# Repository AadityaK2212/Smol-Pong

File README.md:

# Smol-Pong
It is a mini console that can run a 2 player pong game using a coin cell battery and a 8X8 LED grid. ioriginally saw someoemake a smal buiness card that can play video games, so I elaborated off of that and made it to only play pong I also created one for flappy bird. It runs on an ATtiny 1616 Microcontroller.

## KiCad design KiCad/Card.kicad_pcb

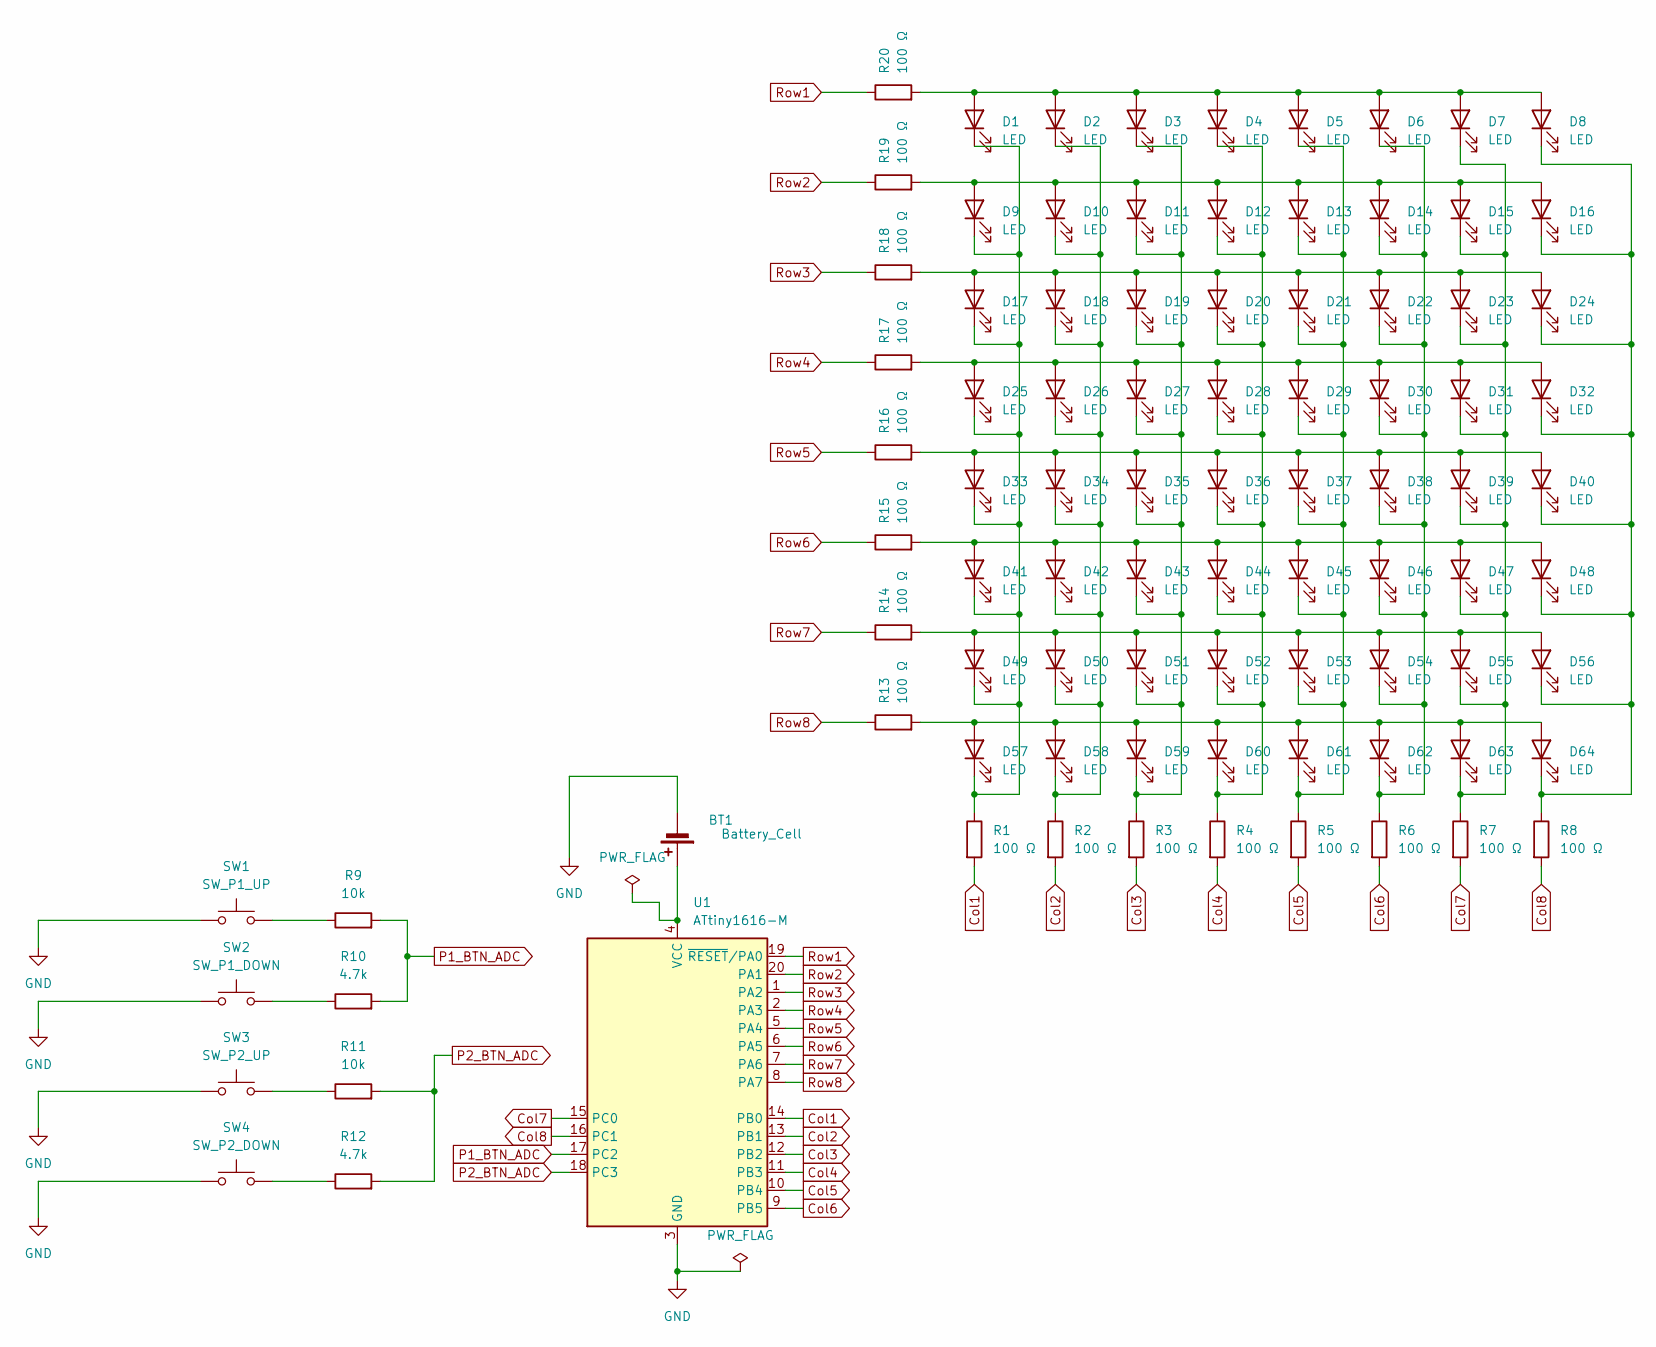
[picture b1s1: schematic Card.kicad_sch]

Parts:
BT1: Battery_Cell; BatteryHolder_Keystone_1057_1x2032
D1, D2, D3, D4, D5, D6, D7, D8, D9, D10, D11, D12, D13, D14, D15, D16, D17, D18, D19, D20, D21, D22, D23, D24, D25, D26, D27, D28, D29, D30, D31, D32, D33, D34, D35, D36, D37, D38, D39, D40, D41, D42, D43, D44, D45, D46, D47, D48, D49, D50, D51, D52, D53, D54, D55, D56, D57, D58, D59, D60, D61, D62, D63, D64: LED; LED_0603_1608Metric
R1, R2, R3, R4, R5, R6, R7, R8, R13, R14, R15, R16, R17, R18, R19, R20: 100 Ω; R_0603_1608Metric
R9, R11: 10k; R_0603_1608Metric
R10, R12: 4.7k; R_0603_1608Metric
SW1: SW_P1_UP; SW_SPST_TL3342
SW2: SW_P1_DOWN; SW_SPST_TL3342
SW3: SW_P2_UP; SW_SPST_TL3342
SW4: SW_P2_DOWN; SW_SPST_TL3342
U1: ATtiny1616-M; VQFN-20-1EP_3x3mm_P0.4mm_EP1.7x1.7mm

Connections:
Col1: R1.2, U1.14 (PB0)
Col2: R2.2, U1.13 (PB1)
Col3: R3.2, U1.12 (PB2)
Col4: R4.2, U1.11 (PB3)
Col5: R5.2, U1.10 (PB4)
Col6: R6.2, U1.9 (PB5)
Col7: R7.2, U1.15 (PC0)
Col8: R8.2, U1.16 (PC1)
GND: BT1.2 (-), SW1.1, SW2.1, SW3.1, SW4.1, U1.3 (GND), U1.21 (GND)
unnamed: BT1.1 (+), U1.4 (VCC)
unnamed: D1.2 (A), D2.2 (A), D3.2 (A), D4.2 (A), D5.2 (A), D6.2 (A), D7.2 (A), D8.2 (A), R20.2
unnamed: D1.1 (K), D9.1 (K), D17.1 (K), D25.1 (K), D33.1 (K), D41.1 (K), D49.1 (K), D57.1 (K), R1.1
unnamed: D9.2 (A), D10.2 (A), D11.2 (A), D12.2 (A), D13.2 (A), D14.2 (A), D15.2 (A), D16.2 (A), R19.2
unnamed: D2.1 (K), D10.1 (K), D18.1 (K), D26.1 (K), D34.1 (K), D42.1 (K), D50.1 (K), D58.1 (K), R2.1
unnamed: D3.1 (K), D11.1 (K), D19.1 (K), D27.1 (K), D35.1 (K), D43.1 (K), D51.1 (K), D59.1 (K), R3.1
unnamed: D4.1 (K), D12.1 (K), D20.1 (K), D28.1 (K), D36.1 (K), D44.1 (K), D52.1 (K), D60.1 (K), R4.1
unnamed: D5.1 (K), D13.1 (K), D21.1 (K), D29.1 (K), D37.1 (K), D45.1 (K), D53.1 (K), D61.1 (K), R5.1
unnamed: D6.1 (K), D14.1 (K), D22.1 (K), D30.1 (K), D38.1 (K), D46.1 (K), D54.1 (K), D62.1 (K), R6.1
unnamed: D7.1 (K), D15.1 (K), D23.1 (K), D31.1 (K), D39.1 (K), D47.1 (K), D55.1 (K), D63.1 (K), R7.1
unnamed: D8.1 (K), D16.1 (K), D24.1 (K), D32.1 (K), D40.1 (K), D48.1 (K), D56.1 (K), D64.1 (K), R8.1
unnamed: D17.2 (A), D18.2 (A), D19.2 (A), D20.2 (A), D21.2 (A), D22.2 (A), D23.2 (A), D24.2 (A), R18.2
unnamed: D25.2 (A), D26.2 (A), D27.2 (A), D28.2 (A), D29.2 (A), D30.2 (A), D31.2 (A), D32.2 (A), R17.2
unnamed: D33.2 (A), D34.2 (A), D35.2 (A), D36.2 (A), D37.2 (A), D38.2 (A), D39.2 (A), D40.2 (A), R16.2
unnamed: D41.2 (A), D42.2 (A), D43.2 (A), D44.2 (A), D45.2 (A), D46.2 (A), D47.2 (A), D48.2 (A), R15.2
unnamed: D49.2 (A), D50.2 (A), D51.2 (A), D52.2 (A), D53.2 (A), D54.2 (A), D55.2 (A), D56.2 (A), R14.2
unnamed: D57.2 (A), D58.2 (A), D59.2 (A), D60.2 (A), D61.2 (A), D62.2 (A), D63.2 (A), D64.2 (A), R13.2
unnamed: R9.1, SW1.2
unnamed: R10.1, SW2.2
unnamed: R11.1, SW3.2
unnamed: R12.1, SW4.2
P1_BTN_ADC: R9.2, R10.2, U1.17 (PC2)
P2_BTN_ADC: R11.2, R12.2, U1.18 (PC3)
Row1: R20.1, U1.19 (~RESET/PA0)
Row2: R19.1, U1.20 (PA1)
Row3: R18.1, U1.1 (PA2)
Row4: R17.1, U1.2 (PA3)
Row5: R16.1, U1.5 (PA4)
Row6: R15.1, U1.6 (PA5)
Row7: R14.1, U1.7 (PA6)
Row8: R13.1, U1.8 (PA7)

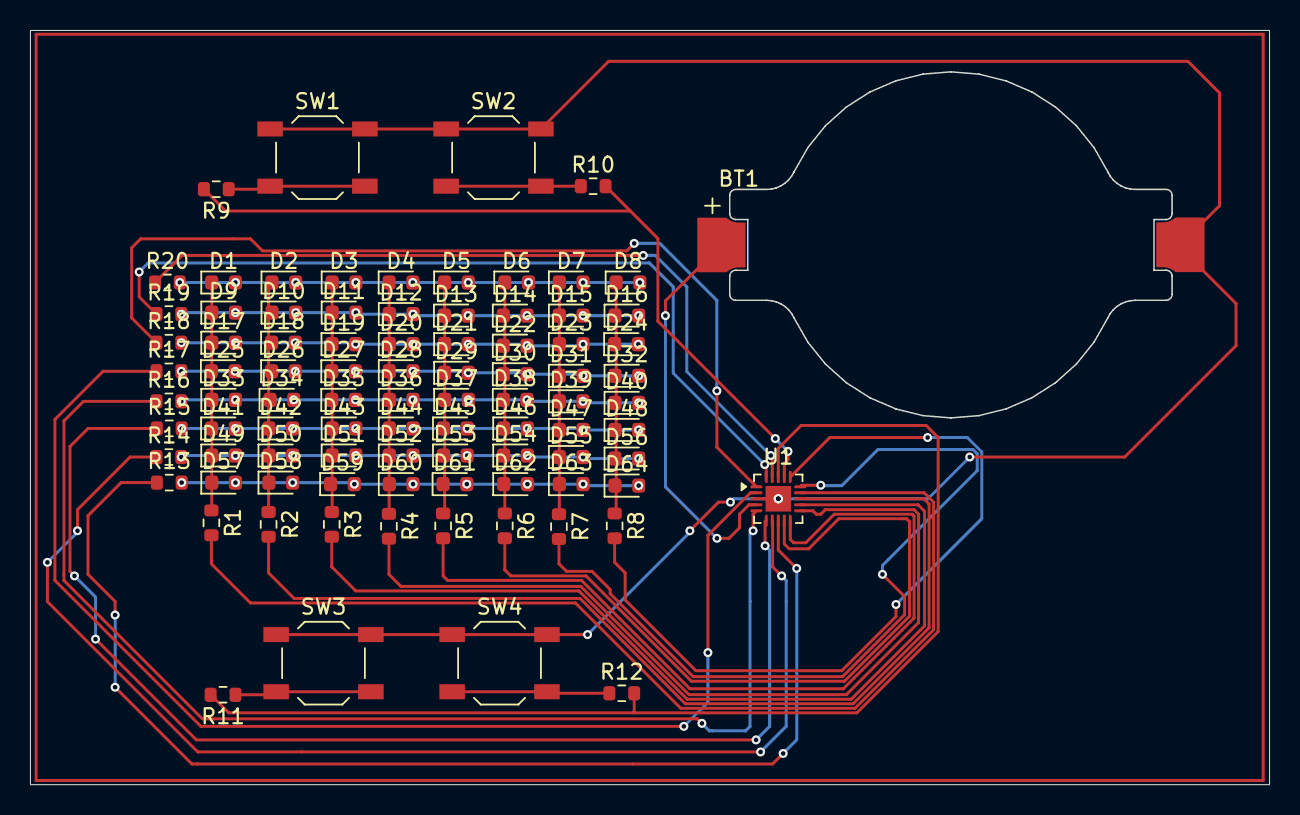
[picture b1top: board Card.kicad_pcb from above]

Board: 2 copper layers, 82.3 x 50.1 mm, 90 parts (0 on the bottom side), 40 nets.

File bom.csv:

Designator,Footprint,Quantity,Value,LCSC Part #
BT1,BatteryHolder_Keystone_1057_1x2032,1,Battery_Cell,
"D1, D10, D11, D12, D13, D14, D15, D16, D17, D18, D19, D2, D20, D21, D22, D23, D24, D25, D26, D27, D28, D29, D3, D30, D31, D32, D33, D34, D35, D36, D37, D38, D39, D4, D40, D41, D42, D43, D44, D45, D46, D47, D48, D49, D5, D50, D51, D52, D53, D54, D55, D56, D57, D58, D59, D6, D60, D61, D62, D63, D64, D7, D8, D9",0603,64,LED,
"R1, R13, R14, R15, R16, R17, R18, R19, R2, R20, R3, R4, R5, R6, R7, R8",0603,16,100 Ω,
SW1,SW_SPST_TL3342,1,SW_P1_UP,
U1,VQFN-20-1EP_3x3mm_P0.4mm_EP1.7x1.7mm,1,ATtiny1616-M,

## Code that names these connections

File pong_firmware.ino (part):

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// resistor ladder so each player only burns one MCU pin.
//
// Hardware notes (from the schematic):
//   - Rows  -> PA0..PA7  (Row1..Row8) -- these are the LED CATHODES
//   - Cols  -> PB0..PB5  (Col1..Col6)
//             PC0 -> Col7
//             PC1 -> Col8                -- columns are the LED ANODES
//   - PC2   -> P1 button ADC node
//   - PC3   -> P2 button ADC node
//
// To light pixel (row, col): drive that column HIGH, that row LOW,
// every other row Hi-Z (or HIGH), every other column LOW.
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
// ---------- pin map ----------
static const uint8_t ROW_PINS[8] = {
  PIN_PA0, PIN_PA1, PIN_PA2, PIN_PA3,
  PIN_PA4, PIN_PA5, PIN_PA6, PIN_PA7
};
static const uint8_t COL_PINS[8] = {
  PIN_PB0, PIN_PB1, PIN_PB2, PIN_PB3,
  PIN_PB4, PIN_PB5, PIN_PC0, PIN_PC1
};

static const uint8_t P1_ADC_PIN = PIN_PC2;
static const uint8_t P2_ADC_PIN = PIN_PC3;

// ---------- ADC thresholds for the resistor-ladder buttons ----------
// Anything below DOWN_MAX -> down, between -> up, above -> nothing.
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
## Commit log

2026-05-06 Add microcontroller information to README
2026-05-06 Create TMP
